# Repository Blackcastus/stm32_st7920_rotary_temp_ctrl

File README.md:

# stm32_st7920_rotary_temp_ctrl
1. Hardware

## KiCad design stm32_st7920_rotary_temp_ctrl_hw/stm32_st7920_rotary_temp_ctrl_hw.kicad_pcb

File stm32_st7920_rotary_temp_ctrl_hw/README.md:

# stm32_st7920_rotary_temp_ctrl_hw

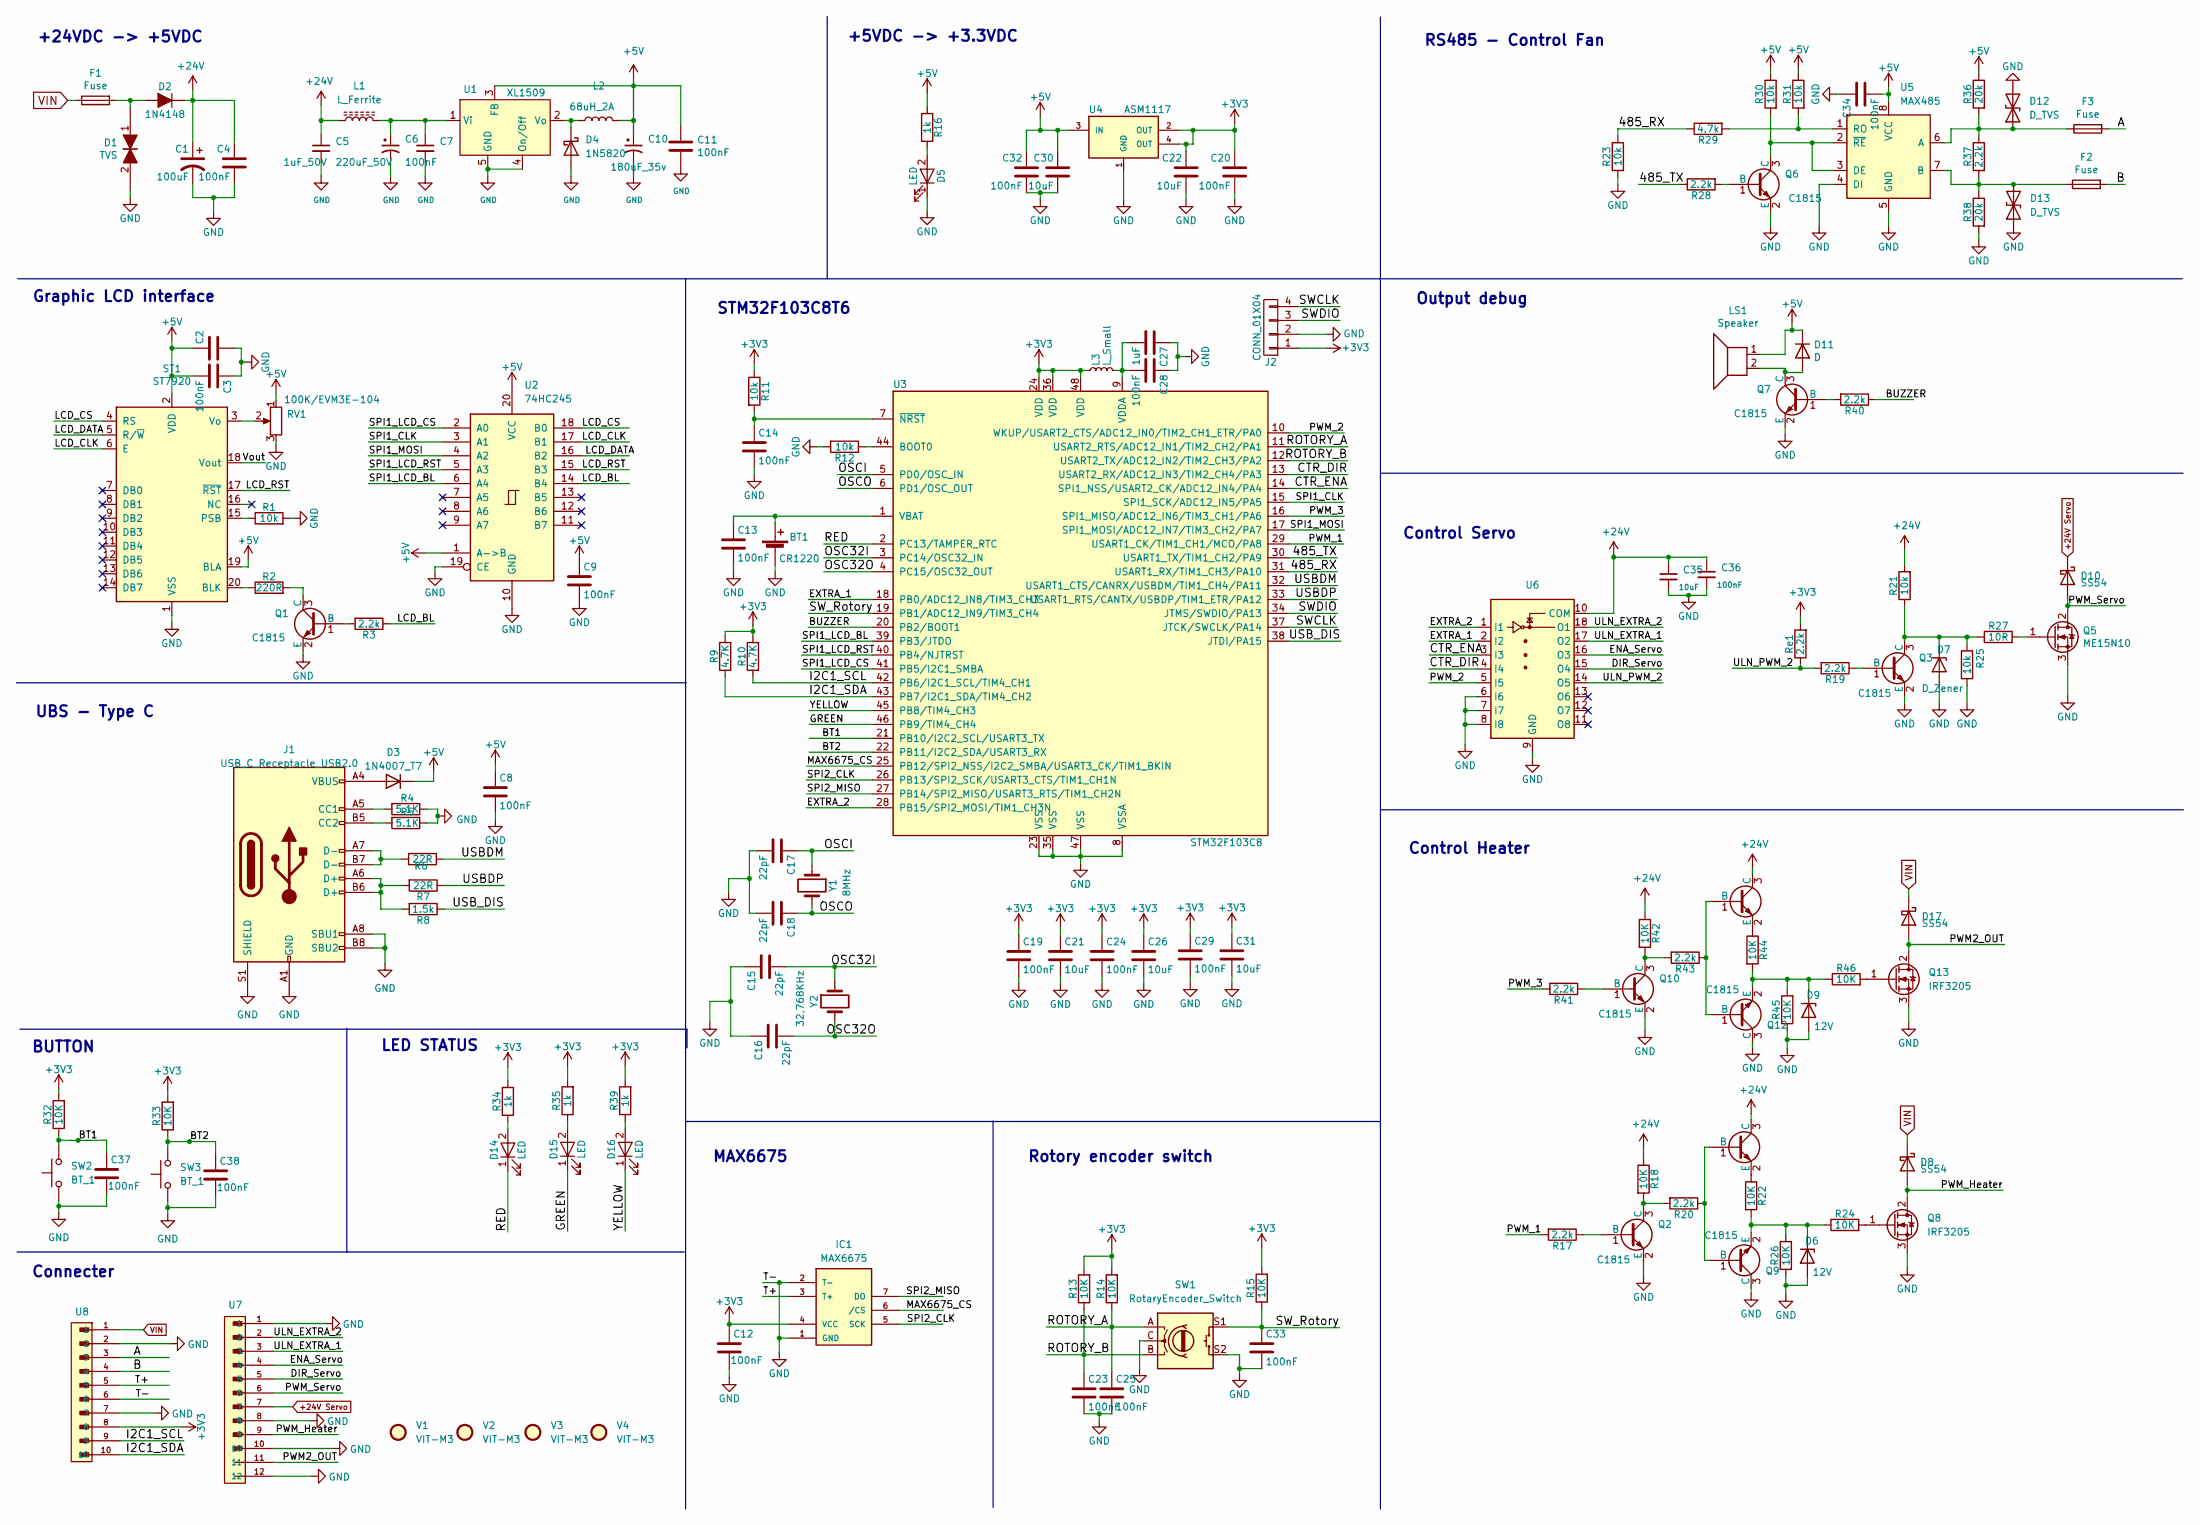
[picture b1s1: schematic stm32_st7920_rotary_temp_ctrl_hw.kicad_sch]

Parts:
BT1: CR1220
C1: 100uF; CP_Elec_8x10.5
C2, C21, C22, C26, C30, C31, C35: 10uF; C_0805_2012Metric_Pad1.18x1.45mm_HandSolder
C3, C4, C7, C8, C9, C11, C12, C13, C14, C19, C20, C23, C24, C25, C28, C29, C32, C33, C34, C36, C37, C38: 100nF; C_0805_2012Metric_Pad1.18x1.45mm_HandSolder
C5: 1uF_50V; C_0805_2012Metric_Pad1.18x1.45mm_HandSolder
C6: 220uF_50V; CP_Elec_8x10.5
C10: 180uF_35v; CP_Elec_6.3x9.9
C15, C16, C17, C18: 22pF; C_0805_2012Metric_Pad1.18x1.45mm_HandSolder
C27: 1uF; C_0805_2012Metric_Pad1.18x1.45mm_HandSolder
D1: TVS; D_SMB
D2: 1N4148; D_SMA
D3: 1N4007_T7; D_SOD-123F
D4: 1N5820; D_SMA
D5: LED; LED_0805_2012Metric_Pad1.15x1.40mm_HandSolder
D6, D9: 12V; D_SC-80_HandSoldering
D7: D_Zener; D_SC-80_HandSoldering
D8, D10, D17: SS54; D_SMA
D11: D; D_SOD-323F
D12, D13: D_TVS; D_SMC
D14, D15, D16: LED; LED_D3.0mm
F1, F2, F3: Fuse; Fuse_1812_4532Metric_Pad1.30x3.40mm_HandSolder
IC1: MAX6675
J1: USB_C_Receptacle_USB2.0; USB_C_Receptacle_GCT_USB4105-xx-A_16P_TopMnt_Horizontal
J2: CONN_01X04; PinHeader_1x04_P2.54mm_Vertical
L1: L_Ferrite; L_Radial_D7.5mm_P3.50mm_Fastron_07P
L2: 68uH_2A; L_Bourns-SRU8028_8.0x8.0mm
L3: L_Small; R_0805_2012Metric_Pad1.20x1.40mm_HandSolder
LS1: Speaker; Buzzer_12x9.5RM7.6
Q1, Q2, Q3, Q4, Q6, Q7, Q9, Q10, Q11, Q12: C1815; SOT-23
Q5: ME15N10; TO-252-2
Q8, Q13: IRF3205; TO-263-2
R1, R11, R12, R21, R23, R25, R30, R31: 10k; R_0805_2012Metric_Pad1.20x1.40mm_HandSolder
R2: 220R; R_0805_2012Metric_Pad1.20x1.40mm_HandSolder
R3, R17, R19, R20, R28, R37, R40, R41, R43: 2.2k; R_0805_2012Metric_Pad1.20x1.40mm_HandSolder
R4, R5: 5.1K; R_0805_2012Metric_Pad1.20x1.40mm_HandSolder
R6, R7: 22R; R_0805_2012Metric_Pad1.20x1.40mm_HandSolder
R8: 1.5k; R_0805_2012Metric_Pad1.20x1.40mm_HandSolder
R9, R10: 4.7K; R_0805_2012Metric_Pad1.20x1.40mm_HandSolder
R13, R14, R15, R18, R22, R24, R26, R32, R33, R42, R44, R45, R46: 10K; R_0805_2012Metric_Pad1.20x1.40mm_HandSolder
R16, R34, R35, R39: 1k; R_0805_2012Metric_Pad1.20x1.40mm_HandSolder
R27: 10R; R_0805_2012Metric_Pad1.20x1.40mm_HandSolder
R29: 4.7k; R_0805_2012Metric_Pad1.20x1.40mm_HandSolder
R36, R38: 20k; R_0805_2012Metric_Pad1.20x1.40mm_HandSolder
RV1: 100K/EVM3E-104; TRIMMER-EVM3E-104
Re1: 2.2k; R_0805_2012Metric_Pad1.20x1.40mm_HandSolder
ST1: ST7920; GLCD-ST7920
SW1: RotaryEncoder_Switch; Rotary-Encoder-SW
SW2, SW3: BT_1; SW_PUSH-12.3mm
U1: XL1509; SOIC-8-1EP_3.9x4.9mm_P1.27mm_EP2.41x3.81mm
U2: 74HC245; HTSSOP-20-1EP_4.4x6.5mm_P0.65mm_EP2.74x3.86mm
U3: STM32F103C8; LQFP-48-1EP_7x7mm_P0.5mm_EP3.6x3.6mm_ThermalVias
U4: ASM1117; SOT-223
U5: MAX485; SO-8_3.9x4.9mm_P1.27mm
U6: ULN2803AD
U7: KF142_12P_5.08
U8: KF142_10P_5.08
V1, V2, V3, V4: VIT-M3
Y1: 8MHz; Crystal_SMD_5032-2Pin_5.0x3.2mm_HandSoldering
Y2: 32,768KHz; Crystal_DS15_D1.5mm_L5.0mm_Horizontal

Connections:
+3V3: C12.1, C19.1, C20.1, C21.1, C22.1, C24.1, C26.1, C29.1, C31.1, IC1.4 (VCC), J2.1, L3.1, R9.2, R10.2, R11.1, R13.2, R14.2, R15.2, R32.2, R33.2, R34.2, R35.2, R39.2, Re1.2, U3.24 (VDD), U3.36 (VDD), U3.48 (VDD), U4.2 (OUT), U4.4 (OUT), U8.8
+5V: C2.1, C3.2, C8.1, C9.1, C10.1, C11.1, C30.1, C32.1, C34.2, D3.1 (K), D11.1 (K), L2.2, LS1.1, R16.2, R30.1, R31.1, R36.1, RV1.1, ST1.2 (VDD), ST1.19 (BLA), U1.3 (FB), U2.1 (A->B), U2.20 (VCC), U4.3 (IN), U5.8 (VCC)
+24V: C1.1, C4.1, C5.1, C35.1, C36.1, D2.1 (K), L1.1, Q4.3 (C), Q11.3 (C), R18.1, R21.2, R42.1, U6.10 (COM)
+24V Servo: D10.1 (K), U7.7
/485_RX: R23.1, R29.1, U3.31 (USART1_RX/TIM1_CH3/PA10)
/485_TX: R28.1, U3.30 (USART1_TX/TIM1_CH2/PA9)
/A: F3.2, U8.3
/B: F2.2, U8.4
/BT1: C37.1, R32.1, SW2.2, U3.21 (PB10/I2C2_SCL/USART3_TX)
/BT2: C38.1, R33.1, SW3.2, U3.22 (PB11/I2C2_SDA/USART3_RX)
/BUZZER: R40.1, U3.20 (PB2/BOOT1)
/CTR_DIR: U3.13 (USART2_RX/ADC12_IN3/TIM2_CH4/PA3), U6.4 (I4)
/CTR_ENA: U3.14 (SPI1_NSS/USART2_CK/ADC12_IN4/PA4), U6.3 (I3)
/DIR_Servo: U6.15 (O4), U7.5
/ENA_Servo: U6.16 (O3), U7.4
/EXTRA_1: U3.18 (PB0/ADC12_IN8/TIM3_CH3), U6.2 (I2)
/EXTRA_2: U3.28 (PB15/SPI2_MOSI/TIM1_CH3N), U6.1 (I1)
/GREEN: D15.1 (K), U3.46 (PB9/TIM4_CH4)
/I2C1_SCL: R10.1, U3.42 (PB6/I2C1_SCL/TIM4_CH1), U8.9
/I2C1_SDA: R9.1, U3.43 (PB7/I2C1_SDA/TIM4_CH2), U8.10
/LCD_BL: R3.1, U2.14 (B4)
/LCD_CLK: ST1.6 (E), U2.17 (B1)
/LCD_CS: ST1.4 (RS), U2.18 (B0)
/LCD_DATA: ST1.5 (R/~W), U2.16 (B2)
/LCD_RST: ST1.17 (~RST), U2.15 (B3)
/MAX6675_CS: IC1.6 (/CS), U3.25 (PB12/SPI2_NSS/I2C2_SMBA/USART3_CK/TIM1_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)
/OSC32I: C15.2, U3.3 (PC14/OSC32_IN), Y2.1
/OSC32O: C16.2, U3.4 (PC15/OSC32_OUT), Y2.2
/OSCI: C17.1, U3.5 (PD0/OSC_IN), Y1.1
/OSCO: C18.1, U3.6 (PD1/OSC_OUT), Y1.2
/PWM2_OUT: D17.2 (A), Q13.2 (D), U7.11
/PWM_1: R17.2, U3.29 (USART1_CK/TIM1_CH1/MCO/PA8)
/PWM_2: U3.10 (WKUP/USART2_CTS/ADC12_IN0/TIM2_CH1_ETR/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), U6.5 (I5)
/PWM_3: R41.2, U3.16 (SPI1_MISO/ADC12_IN6/TIM3_CH1/PA6)
/PWM_Heater: D8.2 (A), Q8.2 (D), U7.9
/PWM_Servo: D10.2 (A), Q5.2 (D), U7.6
/RED: D14.1 (K), U3.2 (PC13/TAMPER_RTC)
/ROTORY_A: C25.1, R14.1, SW1.A, U3.11 (USART2_RTS/ADC12_IN1/TIM2_CH2/PA1)
/ROTORY_B: C23.1, R13.1, SW1.B, U3.12 (USART2_TX/ADC12_IN2/TIM2_CH3/PA2)
/SPI1_CLK: U2.3 (A1), U3.15 (SPI1_SCK/ADC12_IN5/PA5)
/SPI1_LCD_BL: U2.6 (A4), U3.39 (PB3/JTDO)
/SPI1_LCD_CS: U2.2 (A0), U3.41 (PB5/I2C1_SMBA)
/SPI1_LCD_RST: U2.5 (A3), U3.40 (PB4/NJTRST)
/SPI1_MOSI: U2.4 (A2), U3.17 (SPI1_MOSI/ADC12_IN7/TIM3_CH2/PA7)
/SPI2_CLK: IC1.5 (SCK), U3.26 (PB13/SPI2_SCK/USART3_CTS/TIM1_CH1N)
/SPI2_MISO: IC1.7 (DO), U3.27 (PB14/SPI2_MISO/USART3_RTS/TIM1_CH2N)
/SWCLK: J2.4, U3.37 (JTCK/SWCLK/PA14)
/SWDIO: J2.3, U3.34 (JTMS/SWDIO/PA13)
/SW_Rotory: C33.1, R15.1, SW1.S1, U3.19 (PB1/ADC12_IN9/TIM3_CH4)
/T+: IC1.3 (T+), U8.5
/ULN_EXTRA_1: U6.17 (O2), U7.3
/ULN_EXTRA_2: U6.18 (O1), U7.2
/ULN_PWM_2: R19.2, Re1.1, U6.14 (O5)
/USBDM: R6.1, U3.32 (USART1_CTS/CANRX/USBDM/TIM1_CH4/PA11)
/USBDP: R7.1, U3.33 (USART1_RTS/CANTX/USBDP/TIM1_ETR/PA12)
/USB_DIS: R8.1, U3.38 (JTDI/PA15)
/Vout: ST1.18 (Vout)
/YELLOW: D16.1 (K), U3.45 (PB8/TIM4_CH3)
GND: BT1.2 (-), C1.2, C2.2, C3.1, C4.2, C5.2, C6.2, C7.2, C8.2, C9.2, C10.2, C11.2, C12.2, C13.2, C14.2, C15.1, C16.1, C17.2, C18.2, C19.2, C20.2, C21.2, C22.2, C23.2, C24.2, C25.2, C26.2, C27.1, C28.1, C29.2, C30.2, C31.2, C32.2, C33.2, C34.1, C35.2, C36.2, C37.2, C38.2, D1.2, D4.2 (A), D5.1 (K), D6.2 (A), D7.2 (A), D9.2 (A), D12.2 (A2), D13.1 (A1), IC1.1 (GND), IC1.2 (T-), J1.A1 (GND), J1.A8 (SBU1), J1.A12 (GND), J1.B1 (GND), J1.B8 (SBU2), J1.B12 (GND), J1.S1 (SHIELD), J2.2, Q1.2 (E), Q2.2 (E), Q3.2 (E), Q5.3 (S), Q6.2 (E), Q7.2 (E), Q8.3 (S), Q9.3 (C), Q10.2 (E), Q12.3 (C), Q13.3 (S), R1.2, R4.1, R5.1, R12.2, R23.2, R25.1, R26.1, R38.2, R45.1, RV1.3, ST1.1 (VSS), SW1.C, SW1.S2, SW2.1, SW3.1, U1.4 (On/Off), U1.5 (GND), U2.10 (GND), U2.19 (CE), U3.8 (VSSA), U3.23 (VSS), U3.35 (VSS), U3.47 (VSS), U4.1 (GND), U5.4 (DI), U5.5 (GND), U6.6 (I6), U6.7 (I7), U6.8 (I8), U6.9 (GND), U7.1, U7.8, U7.10, U7.12, U8.2, U8.6, U8.7
unnamed: BT1.1 (+), C13.1, U3.1 (VBAT)
unnamed: D1.1, D2.2 (A), F1.2
unnamed: D3.2 (A), J1.A4 (VBUS), J1.A9 (VBUS), J1.B4 (VBUS), J1.B9 (VBUS)
unnamed: D4.1 (K), L2.1, U1.2 (Vo)
unnamed: D5.2 (A), R16.1
unnamed: D6.1 (K), Q9.2 (E), R22.2, R24.1, R26.2
unnamed: D7.1 (K), Q3.3 (C), R21.1, R25.2, R27.1
unnamed: D9.1 (K), Q12.2 (E), R44.2, R45.2, R46.1
unnamed: D11.2 (A), LS1.2, Q7.3 (C)
unnamed: D12.1 (A1), F3.1, R36.2, R37.1, U5.6 (A)
unnamed: D13.2 (A2), F2.1, R37.2, R38.1, U5.7 (B)
unnamed: D14.2 (A), R34.1
unnamed: D15.2 (A), R35.1
unnamed: D16.2 (A), R39.1
unnamed: J1.A5 (CC1), R4.2
unnamed: J1.B5 (CC2), R5.2
unnamed: J1.A6 (D+), J1.B6 (D+), R7.2, R8.2
unnamed: J1.A7 (D-), J1.B7 (D-), R6.2
unnamed: Q1.1 (B), R3.2
unnamed: Q1.3 (C), R2.2
unnamed: Q2.1 (B), R17.1
unnamed: Q2.3 (C), R18.2, R20.2
unnamed: Q3.1 (B), R19.1
unnamed: Q4.1 (B), Q9.1 (B), R20.1
unnamed: Q4.2 (E), R22.1
unnamed: Q5.1 (G), R27.2
unnamed: Q6.1 (B), R28.2
unnamed: Q6.3 (C), R30.2, U5.2 (~RE), U5.3 (DE)
unnamed: Q7.1 (B), R40.2
unnamed: Q8.1 (G), R24.2
unnamed: Q10.1 (B), R41.1
unnamed: Q10.3 (C), R42.2, R43.2
unnamed: Q11.1 (B), Q12.1 (B), R43.1
unnamed: Q11.2 (E), R44.1
unnamed: Q13.1 (G), R46.2
unnamed: R2.1, ST1.20 (BLK)
unnamed: R1.1, ST1.15 (PSB)
unnamed: RV1.2, ST1.3 (Vo)
unnamed: C6.1, C7.1, L1.2, U1.1 (Vi)
unnamed: R12.1, U3.44 (BOOT0)
unnamed: C27.2, C28.2, L3.2, U3.9 (VDDA)
unnamed: C14.1, R11.2, U3.7 (~NRST)
unnamed: R29.2, R31.2, U5.1 (RO)
VIN: D8.1 (K), D17.1 (K), F1.1, U8.1

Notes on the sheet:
Connecter
Control Heater
UBS - Type C
LED STATUS
Graphic LCD interface
Output debug
BUTTON
STM32F103C8T6
+24VDC -> +5VDC
Control Servo
RS485 - Control Fan
Rotory encoder switch
+5VDC -> +3.3VDC
MAX6675

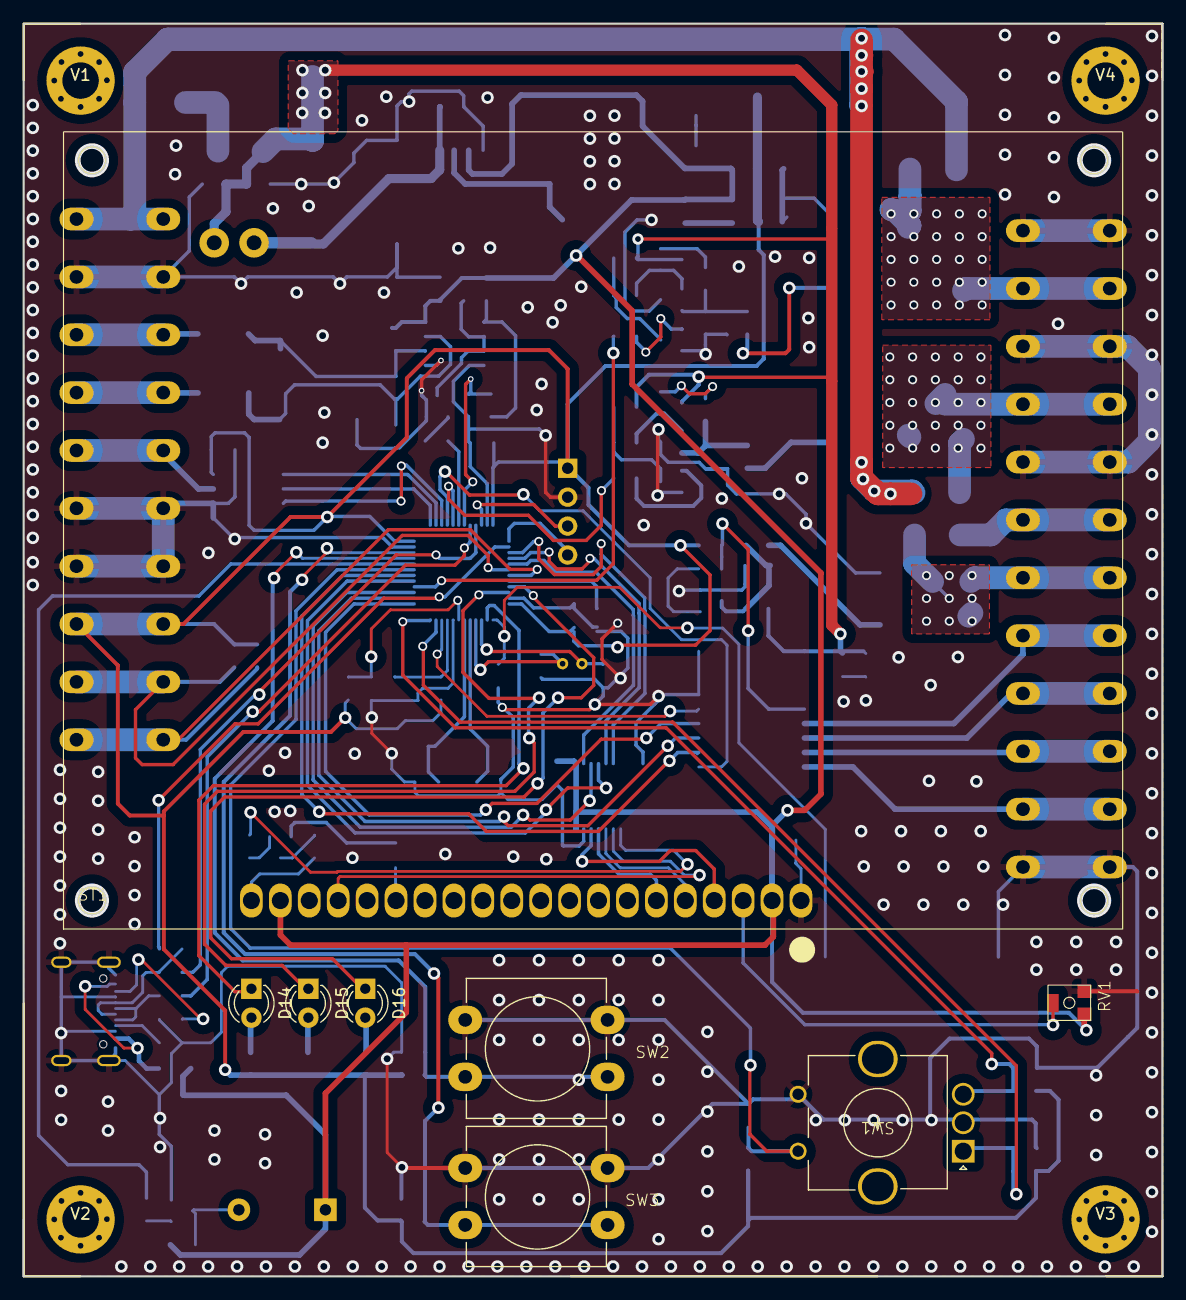
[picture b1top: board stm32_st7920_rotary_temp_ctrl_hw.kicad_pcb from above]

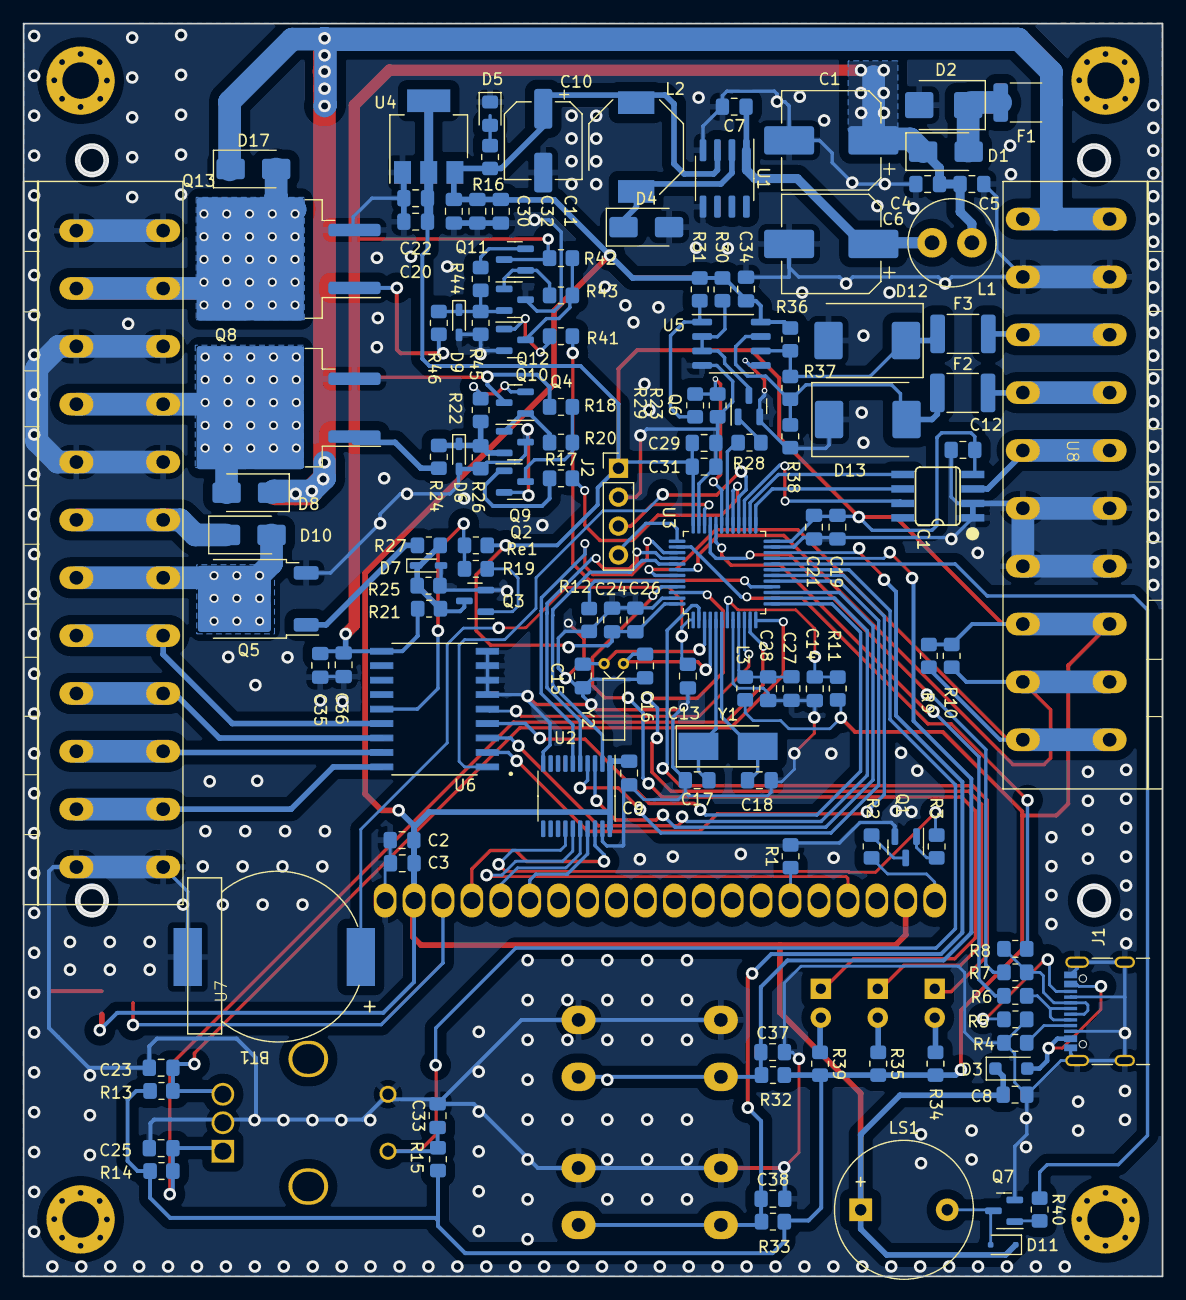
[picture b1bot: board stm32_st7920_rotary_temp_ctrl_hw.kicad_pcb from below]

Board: 2 copper layers, 100.0 x 110.0 mm, 145 parts (133 on the bottom side), 102 nets.

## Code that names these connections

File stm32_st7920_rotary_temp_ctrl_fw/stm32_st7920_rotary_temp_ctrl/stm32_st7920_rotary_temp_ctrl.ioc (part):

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Mcu.Name=STM32F103C(8-B)Tx
Mcu.Package=LQFP48
Mcu.UserName=STM32F103C8Tx
PA0-WKUP.GPIOParameters=GPIO_Label
PA0-WKUP.GPIO_Label=PWM2
PA0-WKUP.Signal=S_TIM2_CH1_ETR
PA1.GPIOParameters=GPIO_Label
PA1.GPIO_Label=ROTORY_A
PA1.Signal=S_TIM2_CH2
PA10.Mode=Asynchronous
PA10.Signal=USART1_RX
PA11.Mode=Device
PA11.Signal=USB_DM
PA12.Mode=Device
PA12.Signal=USB_DP
PA13.Mode=Serial_Wire
PA13.Signal=SYS_JTMS-SWDIO
PA14.Mode=Serial_Wire
PA14.Signal=SYS_JTCK-SWCLK
PA15.GPIOParameters=GPIO_Label
PA15.GPIO_Label=USB_DIS
PA15.Signal=GPIO_Output
PA2.GPIOParameters=GPIO_Label
PA2.GPIO_Label=ROTORY_B
PA2.Signal=S_TIM2_CH3
PA3.GPIOParameters=GPIO_Label
PA3.GPIO_Label=CTR_DIR
PA3.Signal=GPIO_Output
PA4.GPIOParameters=GPIO_Label
PA4.GPIO_Label=CTR_ENA
PA4.Signal=GPIO_Output
PA5.Mode=Simplex_Bidirectional_Master
PA5.Signal=SPI1_SCK
PA6.Signal=S_TIM3_CH1
PA7.Mode=Simplex_Bidirectional_Master
PA7.Signal=SPI1_MOSI
PA8.GPIOParameters=GPIO_Label
PA8.GPIO_Label=PWM1
PA8.Signal=S_TIM1_CH1
PA9.Mode=Asynchronous
PA9.Signal=USART1_TX
PB1.GPIOParameters=GPIO_Label
PB1.GPIO_Label=SW_ROTORY
PB1.Signal=GPIO_Output
PB10.GPIOParameters=GPIO_Label
PB10.GPIO_Label=BT_1
PB10.Signal=GPIO_Input
PB11.GPIOParameters=GPIO_Label
PB11.GPIO_Label=BT_2
PB11.Signal=GPIO_Input
PB12.GPIOParameters=GPIO_Label
PB12.GPIO_Label=MAX6675_CS
PB12.Signal=GPIO_Output
PB13.Mode=Simplex_Bidirectional_Slave
PB13.Signal=SPI2_SCK
PB14.Mode=Simplex_Bidirectional_Slave
PB14.Signal=SPI2_MISO
PB2.GPIOParameters=GPIO_Label
PB2.GPIO_Label=BUZZER_DEBUG
PB2.Signal=GPIO_Output
PB3.GPIOParameters=GPIO_Label
PB3.GPIO_Label=LCD_BL
PB3.Signal=GPIO_Output
PB4.GPIOParameters=GPIO_Label
PB4.GPIO_Label=LCD_RST
PB4.Signal=GPIO_Output
PB5.GPIOParameters=GPIO_Label
PB5.GPIO_Label=LCD_CS
PB5.Signal=GPIO_Output
PB6.Mode=I2C
PB6.Signal=I2C1_SCL
PB7.Mode=I2C
PB7.Signal=I2C1_SDA
PC13-TAMPER-RTC.GPIOParameters=GPIO_Label
PC13-TAMPER-RTC.GPIO_Label=LED_DEBUG
PC13-TAMPER-RTC.Signal=GPIO_Output
PC14-OSC32_IN.Signal=RCC_OSC32_IN
PC15-OSC32_OUT.Signal=RCC_OSC32_OUT
PD0-OSC_IN.Mode=HSE-External-Clock-Source
PD0-OSC_IN.Signal=RCC_OSC_IN
PD1-OSC_OUT.Mode=HSE-External-Clock-Source
PD1-OSC_OUT.Signal=RCC_OSC_OUT
RCC.SYSCLKFreq_VALUE=72000000
RCC.SYSCLKSource=RCC_SYSCLKSOURCE_PLLCLK
board=custom

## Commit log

2023-08-12 start design hardware
2023-08-12 Setup pin/port stm32f103c8t6, design schematic all block
2023-08-14 modify block control servo, block control heater, create button, create 3 led status
2023-08-15 Xep xong linh kien ben PCB, con mot vai output chua cho ra terminal
2023-08-16 Start layout
2023-08-18 finish v1.0
